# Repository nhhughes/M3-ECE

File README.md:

ECE
===

Folders:
  Mixer: for the DCAM.
  PAM: for PAM.
  Richard: for Richard the drummer-bot.

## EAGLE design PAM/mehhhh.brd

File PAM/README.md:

PAM
===

This folder is for PAM, the guitar robot.

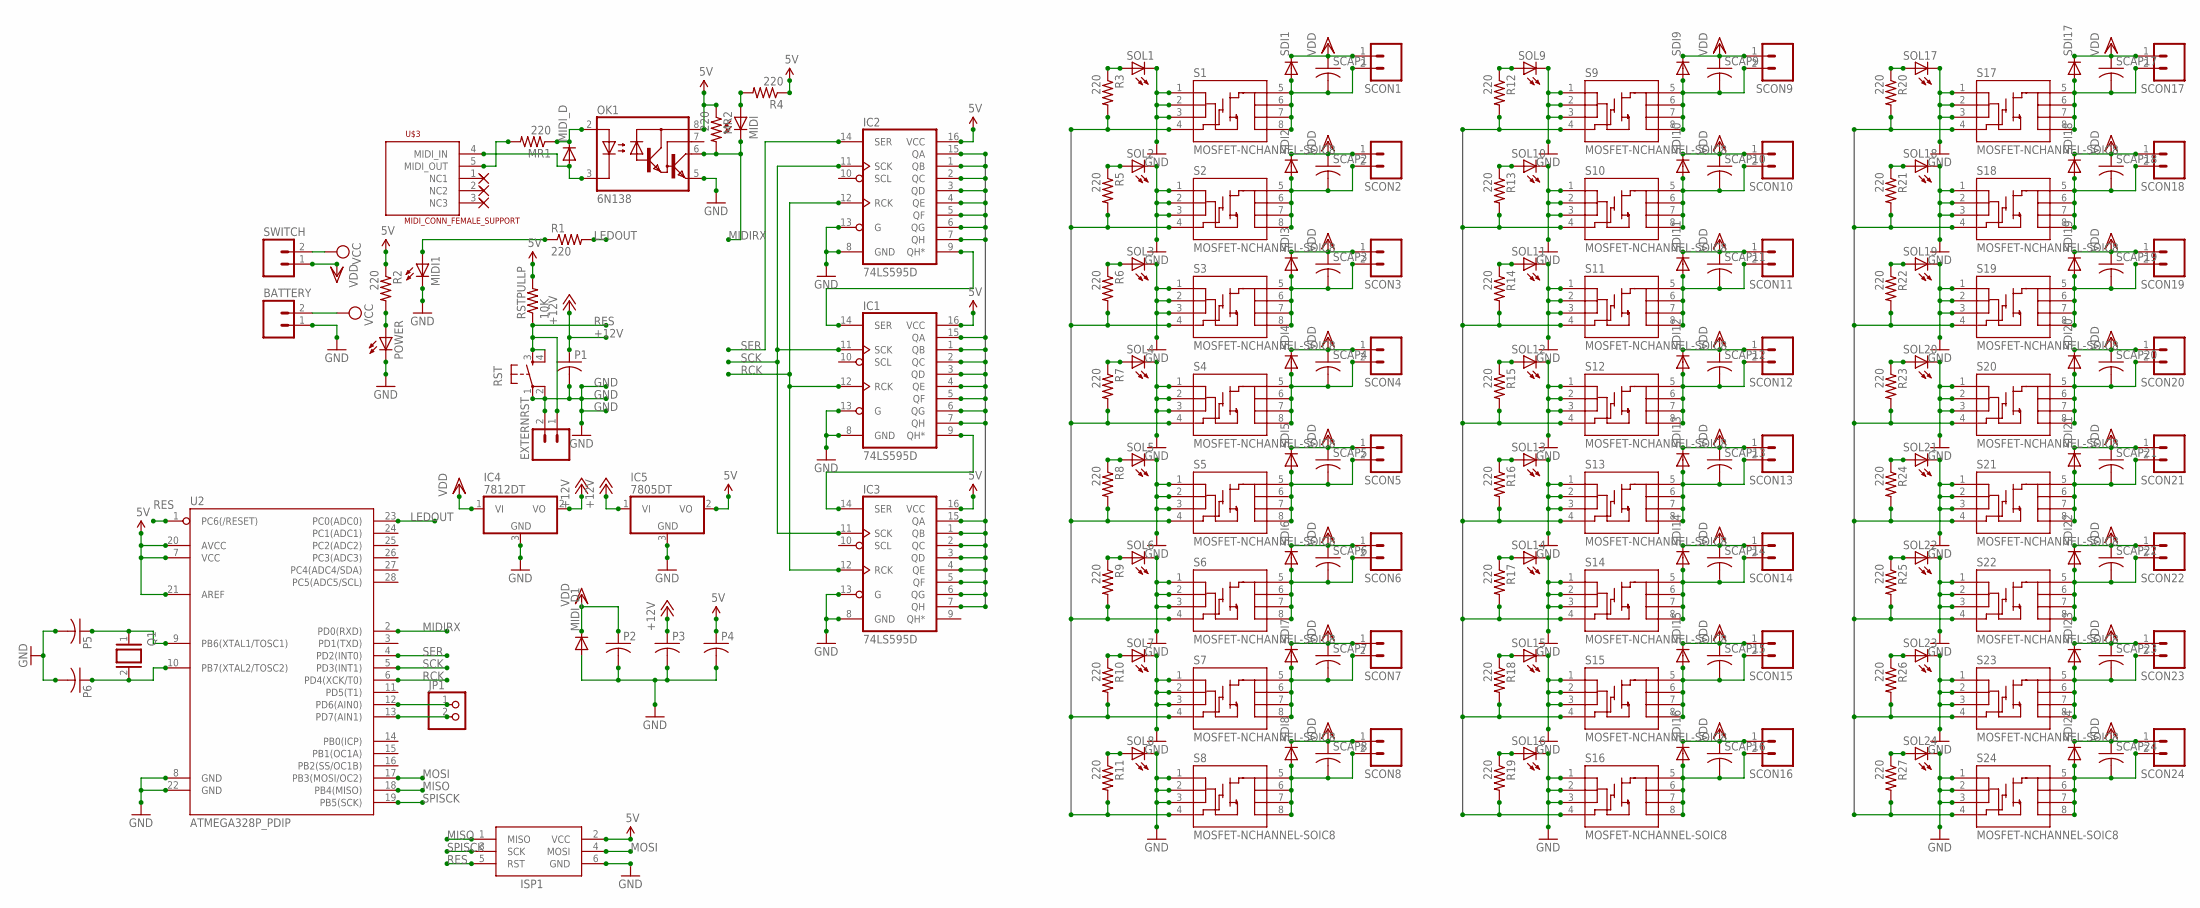
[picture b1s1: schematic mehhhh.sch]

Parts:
BATTERY: M023.5MM; SCREWTERMINAL-3.5MM-2
EXTERNRST: M023.5MM; SCREWTERMINAL-3.5MM-2
IC1, IC2, IC3: 74LS595D; SO16
IC4: 7812DT; TO252
IC5: 7805DT; TO252
ISP1: AVRISP-6; AVRISP
JP1: PINHD-1X2; 1X02
MIDI, MIDI1: LEDCHIPLED_1206; CHIPLED_1206
MIDI_D, MIDI_D1: DIODESMA-ALT; SMA-DIODE_ALT
MR1, MR2: 220; 1206
OK1: 6N138; DIL08
P1, P2, P3, P4, P5, P6: C-USC1206; C1206
POWER: LEDCHIPLED_1206; CHIPLED_1206
Q1: XTAL/S; QS
R1, R2, R3, R4, R5, R6, R7, R8, R9, R10, R11, R12, R13, R14, R15, R16, R17, R18, R19, R20, R21, R22, R23, R24, R25, R26, R27: 220; 1206
RST: TAC_SWITCHPTH; TACTILE-PTH
RSTPULLP: 10K; 1206
S1, S2, S3, S4, S5, S6, S7, S8, S9, S10, S11, S12, S13, S14, S15, S16, S17, S18, S19, S20, S21, S22, S23, S24: MOSFET-NCHANNEL-SOIC8; SO08
SCAP1, SCAP2, SCAP3, SCAP4, SCAP5, SCAP6, SCAP7, SCAP8, SCAP9, SCAP10, SCAP11, SCAP12, SCAP13, SCAP14, SCAP15, SCAP16, SCAP17, SCAP18, SCAP19, SCAP20, SCAP21, SCAP22, SCAP23, SCAP24: C-USC1206; C1206
SCON1, SCON2, SCON3, SCON4, SCON5, SCON6, SCON7, SCON8, SCON9, SCON10, SCON11, SCON12, SCON13, SCON14, SCON15, SCON16, SCON17, SCON18, SCON19, SCON20, SCON21, SCON22, SCON23, SCON24: M023.5MM; SCREWTERMINAL-3.5MM-2
SDI1, SDI2, SDI3, SDI4, SDI5, SDI6, SDI7, SDI8, SDI9, SDI10, SDI11, SDI12, SDI13, SDI14, SDI15, SDI16, SDI17, SDI18, SDI19, SDI20, SDI21, SDI22, SDI23, SDI24: DIODESMA-ALT; SMA-DIODE_ALT
SOL1, SOL2, SOL3, SOL4, SOL5, SOL6, SOL7, SOL8, SOL9, SOL10, SOL11, SOL12, SOL13, SOL14, SOL15, SOL16, SOL17, SOL18, SOL19, SOL20, SOL21, SOL22, SOL23, SOL24: LEDCHIPLED_1206; CHIPLED_1206
SWITCH: M023.5MM; SCREWTERMINAL-3.5MM-2
U2: ATMEGA328P_PDIP; DIL28-3
U$3: MIDI_CONN_FEMALE_SUPPORT; DIN_5_FEMALE_SUPPORT

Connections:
5V: IC1.16 (VCC), IC2.16 (VCC), IC3.16 (VCC), IC5.2 (VO), ISP1.2 (VCC), MR2.1, OK1.8 (VCC), P4.1, R2.1, R4.1, RSTPULLP.2, U2.7 (VCC), U2.20 (AVCC), U2.21 (AREF)
+12V: IC4.2 (VO), IC5.1 (VI), P1.1, P3.1
GND: BATTERY.1, EXTERNRST.2, IC1.8 (GND), IC1.13 (G), IC2.8 (GND), IC2.13 (G), IC3.8 (GND), IC3.13 (G), IC4.3 (GND), IC5.3 (GND), ISP1.6 (GND), MIDI1.C, MIDI_D1.A, OK1.5 (GND), P1.2, P2.2, P3.2, P4.2, P5.2, P6.2, POWER.C, RST.1, RST.2, S1.1 (S), S1.2 (S), S1.3 (S), S2.1 (S), S2.2 (S), S2.3 (S), S3.1 (S), S3.2 (S), S3.3 (S), S4.1 (S), S4.2 (S), S4.3 (S), S5.1 (S), S5.2 (S), S5.3 (S), S6.1 (S), S6.2 (S), S6.3 (S), S7.1 (S), S7.2 (S), S7.3 (S), S8.1 (S), S8.2 (S), S8.3 (S), S9.1 (S), S9.2 (S), S9.3 (S), S10.1 (S), S10.2 (S), S10.3 (S), S11.1 (S), S11.2 (S), S11.3 (S), S12.1 (S), S12.2 (S), S12.3 (S), S13.1 (S), S13.2 (S), S13.3 (S), S14.1 (S), S14.2 (S), S14.3 (S), S15.1 (S), S15.2 (S), S15.3 (S), S16.1 (S), S16.2 (S), S16.3 (S), S17.1 (S), S17.2 (S), S17.3 (S), S18.1 (S), S18.2 (S), S18.3 (S), S19.1 (S), S19.2 (S), S19.3 (S), S20.1 (S), S20.2 (S), S20.3 (S), S21.1 (S), S21.2 (S), S21.3 (S), S22.1 (S), S22.2 (S), S22.3 (S), S23.1 (S), S23.2 (S), S23.3 (S), S24.1 (S), S24.2 (S), S24.3 (S), SOL1.C, SOL2.C, SOL3.C, SOL4.C, SOL5.C, SOL6.C, SOL7.C, SOL8.C, SOL9.C, SOL10.C, SOL11.C, SOL12.C, SOL13.C, SOL14.C, SOL15.C, SOL16.C, SOL17.C, SOL18.C, SOL19.C, SOL20.C, SOL21.C, SOL22.C, SOL23.C, SOL24.C, U2.8 (GND), U2.22 (GND)
LEDOUT: R1.2, U2.23 (PC0(ADC0))
MIDIRX: MIDI.C, MR2.2, OK1.6 (VO), U2.2 (PD0(RXD))
MISO: ISP1.1 (MISO), U2.18 (PB4(MISO))
MOSI: ISP1.4 (MOSI), U2.17 (PB3(MOSI/OC2))
unnamed: MR1.2, U$3.5 (MIDI_OUT)
unnamed: MIDI_D.C, MR1.1, OK1.2 (A)
unnamed: MIDI_D.A, OK1.3 (C), U$3.4 (MIDI_IN)
unnamed: MIDI1.A, R1.1
unnamed: POWER.A, R2.2
unnamed: MIDI.A, R4.2
unnamed: IC1.14 (SER), IC2.9 (QH*)
unnamed: P5.1, Q1.1, U2.9 (PB6(XTAL1/TOSC1))
unnamed: IC1.9 (QH*), IC3.14 (SER)
unnamed: R3.1, SOL1.A
unnamed: S1.5 (D), S1.6 (D), S1.7 (D), S1.8 (D), SCAP1.2, SCON1.2, SDI1.A
unnamed: S2.5 (D), S2.6 (D), S2.7 (D), S2.8 (D), SCAP2.2, SCON2.2, SDI2.A
unnamed: P6.1, Q1.2, U2.10 (PB7(XTAL2/TOSC2))
unnamed: R5.1, SOL2.A
unnamed: S3.5 (D), S3.6 (D), S3.7 (D), S3.8 (D), SCAP3.2, SCON3.2, SDI3.A
unnamed: R6.1, SOL3.A
unnamed: S4.5 (D), S4.6 (D), S4.7 (D), S4.8 (D), SCAP4.2, SCON4.2, SDI4.A
unnamed: R7.1, SOL4.A
unnamed: S5.5 (D), S5.6 (D), S5.7 (D), S5.8 (D), SCAP5.2, SCON5.2, SDI5.A
unnamed: R8.1, SOL5.A
unnamed: S6.5 (D), S6.6 (D), S6.7 (D), S6.8 (D), SCAP6.2, SCON6.2, SDI6.A
unnamed: R9.1, SOL6.A
unnamed: S7.5 (D), S7.6 (D), S7.7 (D), S7.8 (D), SCAP7.2, SCON7.2, SDI7.A
unnamed: R10.1, SOL7.A
unnamed: S8.5 (D), S8.6 (D), S8.7 (D), S8.8 (D), SCAP8.2, SCON8.2, SDI8.A
unnamed: R11.1, SOL8.A
unnamed: S9.5 (D), S9.6 (D), S9.7 (D), S9.8 (D), SCAP9.2, SCON9.2, SDI9.A
unnamed: R12.1, SOL9.A
unnamed: S10.5 (D), S10.6 (D), S10.7 (D), S10.8 (D), SCAP10.2, SCON10.2, SDI10.A
unnamed: R13.1, SOL10.A
unnamed: S11.5 (D), S11.6 (D), S11.7 (D), S11.8 (D), SCAP11.2, SCON11.2, SDI11.A
unnamed: R14.1, SOL11.A
unnamed: S12.5 (D), S12.6 (D), S12.7 (D), S12.8 (D), SCAP12.2, SCON12.2, SDI12.A
unnamed: R15.1, SOL12.A
unnamed: S13.5 (D), S13.6 (D), S13.7 (D), S13.8 (D), SCAP13.2, SCON13.2, SDI13.A
unnamed: R16.1, SOL13.A
unnamed: S14.5 (D), S14.6 (D), S14.7 (D), S14.8 (D), SCAP14.2, SCON14.2, SDI14.A
unnamed: R17.1, SOL14.A
unnamed: S15.5 (D), S15.6 (D), S15.7 (D), S15.8 (D), SCAP15.2, SCON15.2, SDI15.A
unnamed: R18.1, SOL15.A
unnamed: S16.5 (D), S16.6 (D), S16.7 (D), S16.8 (D), SCAP16.2, SCON16.2, SDI16.A
unnamed: R19.1, SOL16.A
unnamed: S17.5 (D), S17.6 (D), S17.7 (D), S17.8 (D), SCAP17.2, SCON17.2, SDI17.A
unnamed: R20.1, SOL17.A
unnamed: S18.5 (D), S18.6 (D), S18.7 (D), S18.8 (D), SCAP18.2, SCON18.2, SDI18.A
unnamed: R21.1, SOL18.A
unnamed: S19.5 (D), S19.6 (D), S19.7 (D), S19.8 (D), SCAP19.2, SCON19.2, SDI19.A
unnamed: R22.1, SOL19.A
unnamed: S20.5 (D), S20.6 (D), S20.7 (D), S20.8 (D), SCAP20.2, SCON20.2, SDI20.A
unnamed: R23.1, SOL20.A
unnamed: S21.5 (D), S21.6 (D), S21.7 (D), S21.8 (D), SCAP21.2, SCON21.2, SDI21.A
unnamed: R24.1, SOL21.A
unnamed: S22.5 (D), S22.6 (D), S22.7 (D), S22.8 (D), SCAP22.2, SCON22.2, SDI22.A
unnamed: R25.1, SOL22.A
unnamed: S23.5 (D), S23.6 (D), S23.7 (D), S23.8 (D), SCAP23.2, SCON23.2, SDI23.A
unnamed: R26.1, SOL23.A
unnamed: S24.5 (D), S24.6 (D), S24.7 (D), S24.8 (D), SCAP24.2, SCON24.2, SDI24.A
unnamed: R27.1, SOL24.A
RCK: IC1.12 (RCK), IC2.12 (RCK), IC3.12 (RCK), U2.6 (PD4(XCK/T0))
RES: EXTERNRST.1, ISP1.5 (RST), RST.3, RST.4, RSTPULLP.1, U2.1 (PC6(/RESET))
S$1: JP1.2, U2.13 (PD7(AIN1)); also elsewhere on the board
S$2: JP1.1, U2.12 (PD6(AIN0)); also elsewhere on the board
SCK: IC1.11 (SCK), IC2.11 (SCK), IC3.11 (SCK), U2.5 (PD3(INT1))
SER: IC2.14 (SER), U2.4 (PD2(INT0))
SHIFTOUT0: IC2.15 (QA), R3.2, S1.4 (G)
SHIFTOUT1: IC2.1 (QB), R5.2, S2.4 (G)
SHIFTOUT2: IC2.2 (QC), R6.2, S3.4 (G)
SHIFTOUT3: IC2.3 (QD), R7.2, S4.4 (G)
SHIFTOUT4: IC2.4 (QE), R8.2, S5.4 (G)
SHIFTOUT5: IC2.5 (QF), R9.2, S6.4 (G)
SHIFTOUT6: IC2.6 (QG), R10.2, S7.4 (G)
SHIFTOUT7: IC2.7 (QH), R11.2, S8.4 (G)
SHIFTOUT8: IC1.15 (QA), R19.2, S16.4 (G)
SHIFTOUT9: IC1.1 (QB), R18.2, S15.4 (G)
SHIFTOUT10: IC1.2 (QC), R17.2, S14.4 (G)
SHIFTOUT11: IC1.3 (QD), R16.2, S13.4 (G)
SHIFTOUT12: IC1.4 (QE), R15.2, S12.4 (G)
SHIFTOUT13: IC1.5 (QF), R14.2, S11.4 (G)
SHIFTOUT14: IC1.6 (QG), R13.2, S10.4 (G)
SHIFTOUT15: IC1.7 (QH), R12.2, S9.4 (G)
SHIFTOUT16: IC3.15 (QA), R20.2, S17.4 (G)
SHIFTOUT17: IC3.1 (QB), R21.2, S18.4 (G)
SHIFTOUT18: IC3.2 (QC), R22.2, S19.4 (G)
SHIFTOUT19: IC3.3 (QD), R23.2, S20.4 (G)
SHIFTOUT20: IC3.4 (QE), R24.2, S21.4 (G)
SHIFTOUT21: IC3.5 (QF), R25.2, S22.4 (G)
SHIFTOUT22: IC3.6 (QG), R26.2, S23.4 (G)
SHIFTOUT23: IC3.7 (QH), R27.2, S24.4 (G)
SPISCK: ISP1.3 (SCK), U2.19 (PB5(SCK))
VCC: BATTERY.2, SWITCH.2
VDD: IC4.1 (VI), MIDI_D1.C, P2.1, SCAP1.1, SCAP2.1, SCAP3.1, SCAP4.1, SCAP5.1, SCAP6.1, SCAP7.1, SCAP8.1, SCAP9.1, SCAP10.1, SCAP11.1, SCAP12.1, SCAP13.1, SCAP14.1, SCAP15.1, SCAP16.1, SCAP17.1, SCAP18.1, SCAP19.1, SCAP20.1, SCAP21.1, SCAP22.1, SCAP23.1, SCAP24.1, SCON1.1, SCON2.1, SCON3.1, SCON4.1, SCON5.1, SCON6.1, SCON7.1, SCON8.1, SCON9.1, SCON10.1, SCON11.1, SCON12.1, SCON13.1, SCON14.1, SCON15.1, SCON16.1, SCON17.1, SCON18.1, SCON19.1, SCON20.1, SCON21.1, SCON22.1, SCON23.1, SCON24.1, SDI1.C, SDI2.C, SDI3.C, SDI4.C, SDI5.C, SDI6.C, SDI7.C, SDI8.C, SDI9.C, SDI10.C, SDI11.C, SDI12.C, SDI13.C, SDI14.C, SDI15.C, SDI16.C, SDI17.C, SDI18.C, SDI19.C, SDI20.C, SDI21.C, SDI22.C, SDI23.C, SDI24.C, SWITCH.1

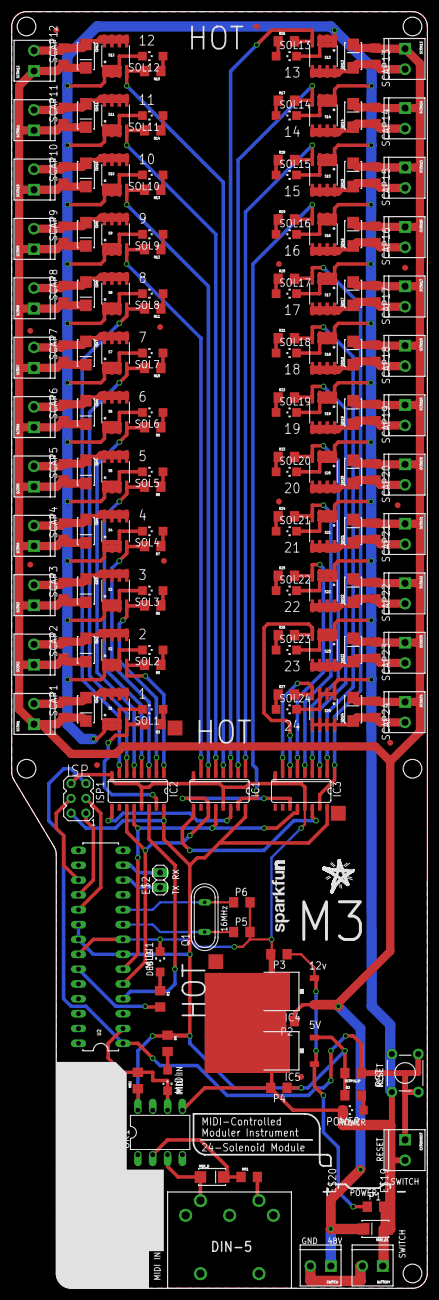
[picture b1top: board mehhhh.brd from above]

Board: 2 copper layers, 71.1 x 218.4 mm, 198 parts (0 on the bottom side), 98 nets.

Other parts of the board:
E$1, E$3, E$4, E$5, E$6, E$7, E$8, E$9, E$10, E$11, E$12, E$13, E$14, E$15, E$16, E$17: FIDUCIAL-1X2
E$2: 1X02
E$18: SFE-NEW-WEB
E$19, E$20: TP07R
E$21: OSHWLOGO_TOL_0.2
E$22: STARBOARD_LOGO
U$1: LOGO

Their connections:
S$1: E$2.2; also elsewhere on the board
S$2: E$2.1; also elsewhere on the board

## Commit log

2013-01-31 Added directories for PAM and the mixer.
2013-01-31 Added directory for Richard the drum kit robot.
2013-02-18 Added stuff for Richard

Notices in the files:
parts and their libraries:
SparkFun: Licensing: CC v3.0 Share-Alike You are welcome to use this library for commercial purposes.
